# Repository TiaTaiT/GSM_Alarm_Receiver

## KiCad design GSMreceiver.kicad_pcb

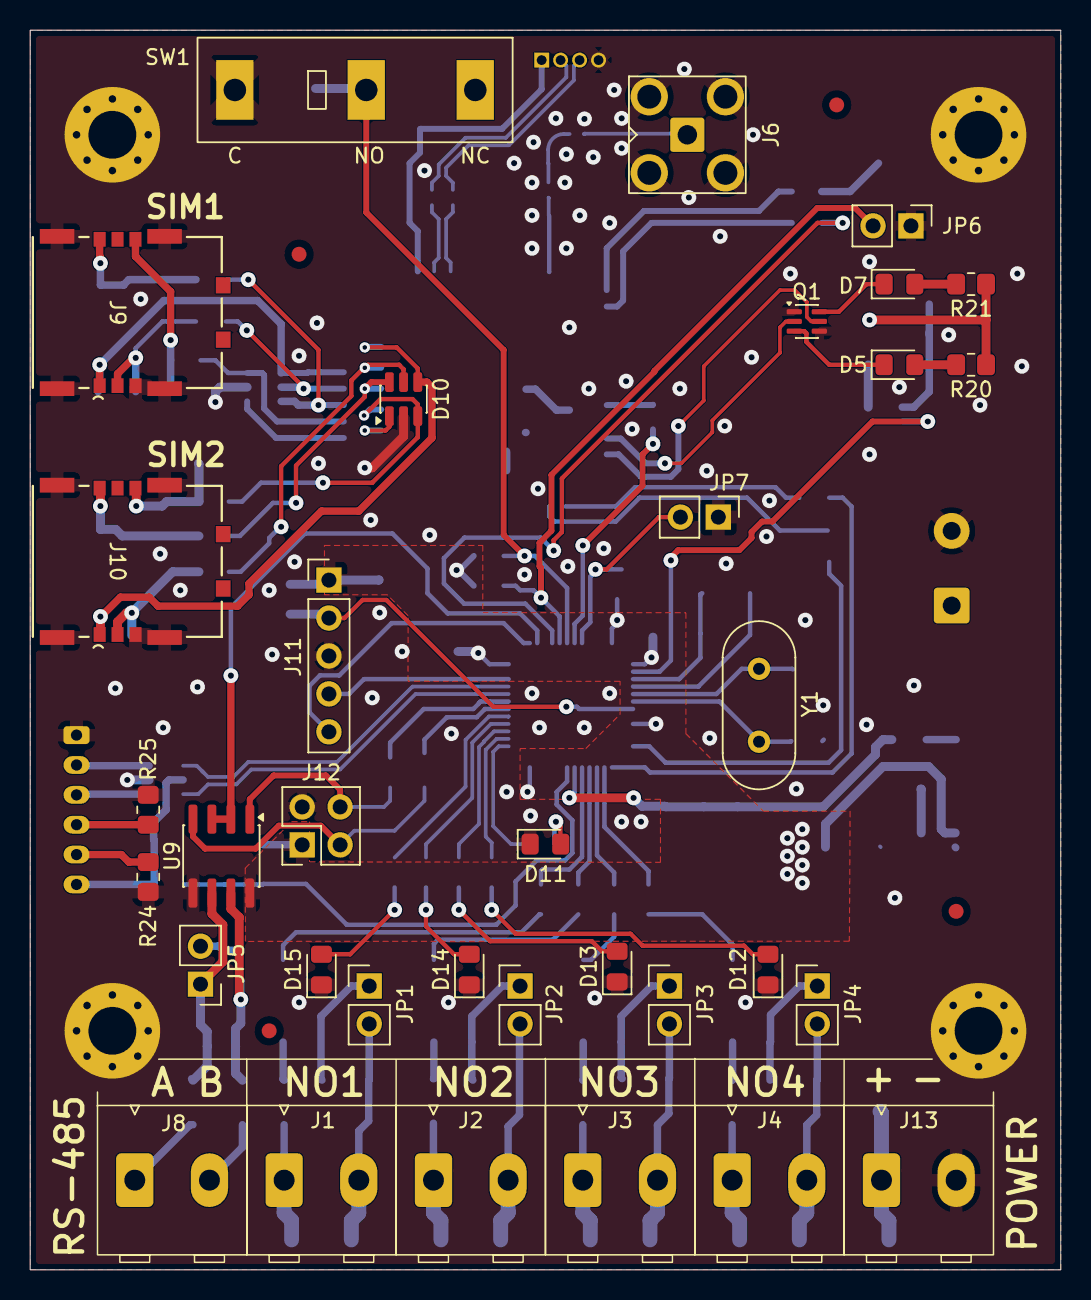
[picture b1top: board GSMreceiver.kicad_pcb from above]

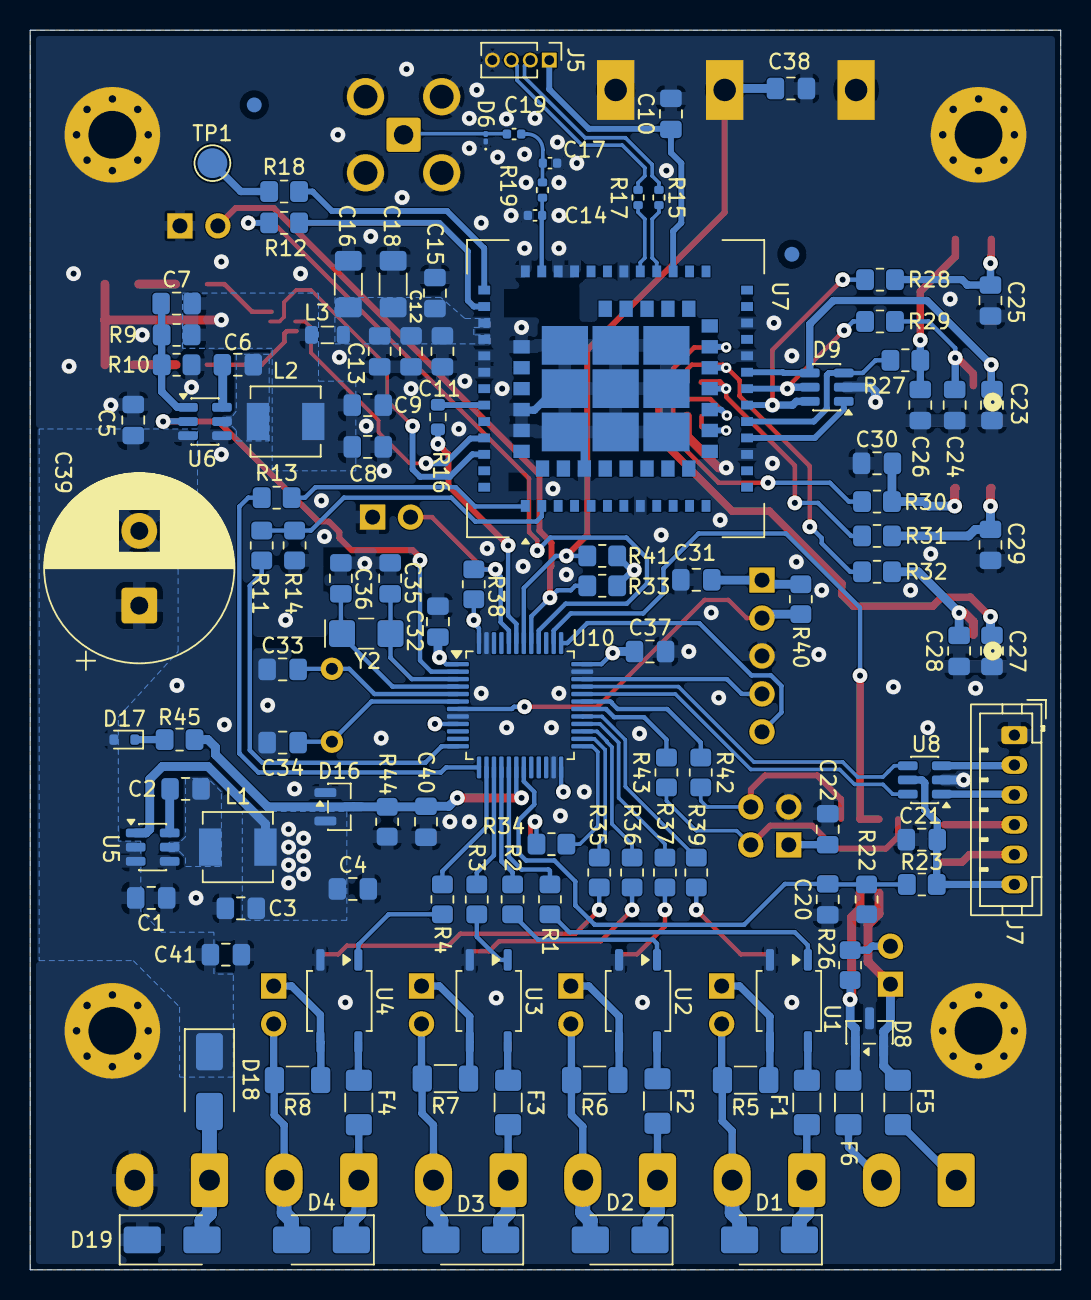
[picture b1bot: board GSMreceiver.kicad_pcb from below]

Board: 2 copper layers, 69.0 x 83.0 mm, 159 parts (117 on the bottom side), 116 nets.

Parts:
C1, C5: 10uF; C_0805_2012Metric_Pad1.18x1.45mm_HandSolder
C2, C6, C10, C13, C20, C21, C22, C23, C27, C31, C32, C37, C38, C40: 100nF; C_0805_2012Metric_Pad1.18x1.45mm_HandSolder
C3, C4, C8, C9: 22uF; C_0805_2012Metric_Pad1.18x1.45mm_HandSolder
C7: 100pF; C_0805_2012Metric_Pad1.18x1.45mm_HandSolder
C11: 10pF; C_0805_2012Metric_Pad1.18x1.45mm_HandSolder
C12: 33pF; C_0805_2012Metric_Pad1.18x1.45mm_HandSolder
C14, C17: 10pF; C_0402_1005Metric
C15: 1 uF; C_0805_2012Metric_Pad1.18x1.45mm_HandSolder
C16, C18: 100 uF; C_1206_3216Metric_Pad1.33x1.80mm_HandSolder
C19: 100pF; C_0402_1005Metric
C24, C25, C26, C28, C29, C30: 22pF; C_0805_2012Metric_Pad1.18x1.45mm_HandSolder
C33, C34: 20pF; C_0805_2012Metric_Pad1.18x1.45mm_HandSolder
C35, C36: 12.5pF; C_0805_2012Metric_Pad1.18x1.45mm_HandSolder
C39: 1000uFx35V; CP_Radial_D12.5mm_P5.00mm
C41: 470nFx50V; C_0805_2012Metric_Pad1.18x1.45mm_HandSolder
D1, D2, D3, D4, D19: SMAJ30CA; D_SMA
D5: STATUS; LED_0805_2012Metric_Pad1.15x1.40mm_HandSolder
D6: LXES1UTAA1-157; D_01005_0402Metric
D7: NETLIGHT; LED_0805_2012Metric_Pad1.15x1.40mm_HandSolder
D8: SM712-02HTG; SOT-23
D9, D10: ESDA6V1-5SC6; SOT-23-6
D11, D12, D13, D14: FYLS-0805GC; LED_0805_2012Metric_Pad1.15x1.40mm_HandSolder
D15: FYLS-0805SRC; LED_0805_2012Metric_Pad1.15x1.40mm_HandSolder
D16: BAS40-04; SOT-23
D17: 1N4148WT; D_SOD-523
D18: SS26; D_SMA
F1, F2, F3, F4, F5, F6: 1206L005/60WR; Fuse_1206_3216Metric_Pad1.42x1.75mm_HandSolder
FID1, FID2, FID3, FID4, FID5, FID6: Fiducial; Fiducial_1mm_Mask2mm
H1, H2, H3, H4: MountingHole_Pad; MountingHole_3.2mm_M3_Pad_Via
J1: Relay_1; DEGSON_DG390-5.0-02P_1x02_P5.0mm_Vertical
J2: Relay_2; DEGSON_DG390-5.0-02P_1x02_P5.0mm_Vertical
J3: Relay_3; DEGSON_DG390-5.0-02P_1x02_P5.0mm_Vertical
J4: Relay_4; DEGSON_DG390-5.0-02P_1x02_P5.0mm_Vertical
J5: USB_RF; PinHeader_1x04_P1.27mm_Vertical
J6: RF Antenna; SMA_HJ-SMA405
J7: USB-C; JST_PH_B6B-PH-K_1x06_P2.00mm_Vertical
J8: RS485; DEGSON_DG390-5.0-02P_1x02_P5.0mm_Vertical
J9, J10: 1042240820; 1042240820_MOLEX
J11: SWD; PinHeader_1x05_P2.54mm_Vertical
J12: UART1; PinSocket_2x02_P2.54mm_Vertical
J13: DG390-5.0-02P; DEGSON_DG390-5.0-02P_1x02_P5.0mm_Vertical
JP1, JP2, JP3, JP4, JP5, JP6, JP7: Jumper_2_Open; PinHeader_1x02_P2.54mm_Vertical
L1: CSAB0420-3R3M; CSAB0420-4.4x4.4mm
L2: CSAB0420-100M; CSAB0420-4.4x4.4mm
L3: BLM21PG300SN1D; L_0805_2012Metric
Q1: MUN5233DW1; SOT-363_SC-70-6
R1, R2, R3, R4: 2.7k; R_0805_2012Metric_Pad1.20x1.40mm_HandSolder
R5, R6, R7, R8: 4.7k; R_1206_3216Metric_Pad1.30x1.75mm_HandSolder
R9: 205k; R_0805_2012Metric_Pad1.20x1.40mm_HandSolder
R10: 51k; R_0805_2012Metric_Pad1.20x1.40mm_HandSolder
R11, R12, R13, R18: 1k; R_0805_2012Metric_Pad1.20x1.40mm_HandSolder
R14: 5.6k; R_0805_2012Metric_Pad1.20x1.40mm_HandSolder
R15, R17, R19: 0; R_0402_1005Metric
R16: 1k; R_0603_1608Metric
R20, R21: 470; R_0805_2012Metric_Pad1.20x1.40mm_HandSolder
R22: 47k; R_0805_2012Metric_Pad1.20x1.40mm_HandSolder
R23, R33, R38, R40, R41, R44: 100k; R_0805_2012Metric_Pad1.20x1.40mm_HandSolder
R24, R25: 5.1k; R_0805_2012Metric_Pad1.20x1.40mm_HandSolder
R26: 120; R_0805_2012Metric_Pad1.20x1.40mm_HandSolder
R27, R28, R29, R30, R31, R32, R42, R43: 51; R_0805_2012Metric_Pad1.20x1.40mm_HandSolder
R34, R35, R36, R37: 330; R_0805_2012Metric_Pad1.20x1.40mm_HandSolder
R39: 510; R_0805_2012Metric_Pad1.20x1.40mm_HandSolder
R45: 1M; R_0805_2012Metric_Pad1.20x1.40mm_HandSolder
SW1: SM5-180UP-1; SW_XKB_SM5-180UP-1
TP1: USB_BOOT; TestPoint_Pad_D2.0mm
U1, U2, U3, U4: PRAB34S; SOP-4_3.8x4.1mm_P2.54mm
U5: AP63203WU; TSOT-23-6
U6: AP63200WU; TSOT-23-6
U7: A7682E; SIMCom_A7682E_LGA-85
U8: USBLC6-2SC6; SOT-23-6
U9: XR3072XIDTR-F; SOIC-8_3.9x4.9mm_P1.27mm
U10: STM32L072CBT6; LQFP-48_7x7mm_P0.5mm
Y1: 4 MHz; Crystal_HC49-4H_Vertical
Y2: 32768 kHz; Crystal_SMD_EuroQuartz_EQ161-2Pin_3.2x1.5mm_HandSoldering

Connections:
+3V3: C3.2, C4.2, C22.2, C31.2, C32.2, C37.1, D16.2, J11.1, J12.1, L1.2, R33.1, R38.1, R40.1, R41.1, U5.1 (FB), U9.8 (VCC), U10.1 (VDD), U10.9 (VDDA), U10.24 (VDD), U10.36 (VDD_USB), U10.48 (VDD)
+4V: C7.2, C8.2, C9.2, L2.2, L3.2, R9.2, R20.1, R21.1
/4V_ENABLE: U6.2 (EN), U10.2 (PC13)
/BATTERY_LEVEL: C40.2, D16.3, R44.1, R45.1, U10.18 (PB0)
/DOUT1: R1.1, U10.17 (PA7)
/DOUT2: R2.1, U10.16 (PA6)
/DOUT3: R3.1, U10.15 (PA5)
/DOUT4: R4.1, U10.14 (PA4)
/IN_OUT/RELAY1A: D1.2 (A2), J1.2, JP1.2 (B), R5.2
/IN_OUT/RELAY1B: D1.1 (A1), F1.2, J1.1
/IN_OUT/RELAY2A: D2.2 (A2), J2.2, JP2.2 (B), R6.2
/IN_OUT/RELAY2B: D2.1 (A1), F2.2, J2.1
/IN_OUT/RELAY3A: D3.2 (A2), J3.2, JP3.2 (B), R7.2
/IN_OUT/RELAY3B: D3.1 (A1), F3.2, J3.1
/IN_OUT/RELAY4A: D4.2 (A2), J4.2, JP4.2 (B), R8.2
/IN_OUT/RELAY4B: D4.1 (A1), F4.2, J4.1
/MCU/BOOT0: JP7.2 (B), R38.2, U10.44 (BOOT0)
/MCU/LED1: R34.1, U10.25 (PB12)
/MCU/LED2: R35.1, U10.26 (PB13)
/MCU/LED3: R36.1, U10.27 (PB14)
/MCU/LED4: R37.1, U10.28 (PB15)
/MCU/LED5: R39.1, U10.29 (PA8)
/MCU/NRST: J11.2, R40.2, U10.7 (NRST)
/MCU/SWCLK: J11.5, U10.37 (PA14)
/MCU/SWDIO: J11.4, U10.34 (PA13)
/MCU/TAMPER: C38.2, R41.2, SW1.2 (B), U10.42 (PB6)
/MCU/VBUS_SENSING: C20.2, R22.1, R23.1, U10.19 (PB1)
/Power_3.3V (page 3)/3V3-BST: C2.1, U5.6 (BST)
/Power_3.3V (page 3)/3V3-SW: C2.2, L1.1, U5.5 (SW)
/Power_3.3V (page 3)/VBAT_IN: C1.2, C5.2, C39.1, C41.1, D17.2 (A), D18.1 (K), U5.2 (EN), U5.3 (IN), U6.3 (IN)
/Power_4V/4V-FB: C7.1, R9.1, R10.2, U6.1 (FB)
/Power_4V/4V-SW: C6.2, L2.1, U6.5 (SW)
/Power_input/Vsupply: D18.2 (A), D19.2 (A2), J13.1
/RF_ENABLE: R16.1, U10.43 (PB7)
/RF_RESET: R12.1, U10.40 (PB4)
/RFmodule/BOOT: R18.1, TP1.1 (1_1)
/RFmodule/NETLIGHT: Q1.2 (B), U7.41 (NETLIGHT)
/RFmodule/RF_USB_N: J5.2, R15.1
/RFmodule/RF_USB_P: J5.3, R17.1
/RFmodule/SIM1_CLK: D9.6 (IO5), R28.1, U7.16 (SIM1_CLK)
/RFmodule/SIM1_DATA: D9.3 (IO2), R27.1, U7.15 (SIM1_DATA)
/RFmodule/SIM1_DET: D9.1 (IO1), U7.14 (SIM1_DET)
/RFmodule/SIM1_RST: D9.5 (IO4), R29.1, U7.17 (SIM1_RST)
/RFmodule/SIM1_VDD: C23.2, D9.4 (IO3), J9.S1 (VCC), U7.18 (SIM1_VDD)
/RFmodule/SIM2_CLK: D10.6 (IO5), R31.1, U7.54 (SIM2_CLK)
/RFmodule/SIM2_DATA: D10.3 (IO2), R30.1, U7.53 (SIM2_DATA)
/RFmodule/SIM2_DET: D10.1 (IO1), U7.52 (SIM2_DET)
/RFmodule/SIM2_RST: D10.5 (IO4), R32.1, U7.55 (SIM2_RST)
/RFmodule/SIM2_VDD: C27.2, D10.4 (IO3), J10.S1 (VCC), U7.56 (SIM2_VDD)
/RFmodule/SIM_USB_N: R15.2, U7.25 (USB_DP)
/RFmodule/SIM_USB_P: R17.2, U7.26 (USB_DM)
/RFmodule/STATUS: Q1.5 (B), U7.42 (STATUS)
/RFmodule/USB_VBUS: C10.1, J5.1, U7.24 (USB_VBUS)
/RFmodule/VBAT: C11.2, C12.2, C13.2, C15.2, C16.2, C18.2, L3.1, U7.34 (VBAT), U7.35 (VBAT)
/RS485/RS485+: F5.2, J8.1
/RS485/RS485-: F6.2, J8.2
/RS485/RS485_N: D8.1 (A1), F6.1, R26.1, U9.7 (B)
/RS485/RS485_P: D8.2 (A2), F5.1, JP5.1 (A), U9.6 (A)
/RS485_EN: U9.2 (~RE), U9.3 (DE), U10.38 (PA15)
/SIMcard1/CARD_CLK: C25.2, J9.S3 (CLK), R28.2
/SIMcard1/CARD_DATA: C26.2, J9.S6 (I/O), R27.2
/SIMcard1/CARD_RST: C24.2, J9.S2 (RST), R29.2
/SIMcard2/CARD_CLK: C29.2, J10.S3 (CLK), R31.2
/SIMcard2/CARD_DATA: C30.2, J10.S6 (I/O), R30.2
/SIMcard2/CARD_RST: C28.2, J10.S2 (RST), R32.2
/UART1_RX: J12.4, R42.2, U9.1 (RO)
/UART1_TX: J12.2, R43.2, U9.4 (DI)
/UART2_RX: R13.1, U10.13 (PA3)
/UART2_TX: R11.1, U10.12 (PA2)
/USB/USB_CC1: J7.5, R24.1
/USB/USB_CC2: J7.4, R25.1
/USB/USB_N: J7.3, U8.1 (I/O1)
/USB/USB_P: J7.2, U8.3 (I/O2)
/USB/USB_VBUS: C21.2, J7.6, R23.2, U8.5 (VBUS)
/USB_D+: U8.4 (I/O2), U10.33 (PA12)
/USB_D-: U8.6 (I/O1), U10.32 (PA11)
GNDD: C1.1, C3.1, C4.1, C5.1, C8.1, C9.1, C10.2, C11.1, C12.1, C13.1, C14.1, C15.1, C16.1, C17.1, C18.1, C20.1, C21.1, C22.1, C23.1, C24.1, C25.1, C26.1, C27.1, C28.1, C29.1, C30.1, C31.1, C32.1, C33.1, C34.1, C35.1, C36.1, C37.2, C38.1, C39.2, C40.1, C41.2, D6.1 (A1), D8.3 (common), D9.2 (GND), D10.2 (GND), D11.1 (K), D12.1 (K), D13.1 (K), D14.1 (K), D15.1 (K), D16.1, D19.1 (A1), H1.1 (1_1), H2.1 (1_1), H3.1 (1_1), H4.1 (1_1), J5.4, J6.2 (Ext), J7.1, J9.G (SH), J9.S4 (GND), J10.G (SH), J10.S4 (GND), J11.3, J12.3, J13.2, JP6.1 (A), JP7.1 (A), Q1.1 (E), Q1.4 (E), R10.1, R14.1, R22.2, R24.2, R25.2, R44.2, SW1.1 (A), U1.2 (C), U2.2 (C), U3.2 (C), U4.2 (C), U5.4 (GND), U6.4 (GND), U7.8 (GND), U7.13 (GND), U7.19 (GND), U7.21 (GND), U7.27 (GND), U7.30 (GND), U7.31 (GND), U7.33 (GND), U7.36 (GND), U7.37 (GND), U7.45 (GND), U7.63 (GND), U7.66 (GND), U7.67 (GND), U7.69 (GND), U7.70 (GND), U7.71 (GND), U7.72 (GND), U7.73 (GND), U7.74 (GND), U7.75 (GND), U7.76 (GND), U7.77 (GND), U8.2 (GND), U9.5 (GND), U10.8 (VSSA), U10.23 (VSS), U10.35 (VSS), U10.47 (VSS)
unnamed: C17.2, C19.2, R19.2
unnamed: D5.2 (A), R20.2
unnamed: D5.1 (K), Q1.3 (C)
unnamed: C19.1, D6.2 (A2), J6.1 (In)
unnamed: D7.2 (A), R21.2
unnamed: D7.1 (K), Q1.6 (C)
unnamed: D11.2 (A), R34.2
unnamed: D12.2 (A), R35.2
unnamed: D13.2 (A), R36.2
unnamed: D14.2 (A), R37.2
unnamed: D15.2 (A), R39.2
unnamed: D17.1 (K), R45.2
unnamed: JP1.1 (A), R5.1, U1.3 (VCC)
unnamed: JP2.1 (A), R6.1, U2.3 (VCC)
unnamed: JP3.1 (A), R7.1, U3.3 (VCC)
unnamed: JP4.1 (A), R8.1, U4.3 (VCC)
unnamed: JP5.2 (B), R26.2
unnamed: JP6.2 (B), R33.2, U10.41 (PB5)
unnamed: R1.2, U1.1 (A)
unnamed: F1.1, U1.4 (VEE)
unnamed: R2.2, U2.1 (A)
unnamed: F2.1, U2.4 (VEE)
unnamed: R3.2, U3.1 (A)
unnamed: F3.1, U3.4 (VEE)
unnamed: R4.2, U4.1 (A)
unnamed: F4.1, U4.4 (VEE)
unnamed: C6.1, U6.6 (BST)
unnamed: R18.2, U7.82 (BOOT_CFG)
unnamed: C14.2, R19.1, U7.32 (RF_ANT)
unnamed: R11.2, R14.2, U7.2 (UART1_RXD)
unnamed: R13.2, U7.1 (UART1_TXD)
unnamed: R16.2, U7.39 (~PWRKEY)
unnamed: R12.2, U7.83 (~RESET)
unnamed: R43.1, U10.30 (PA9)
unnamed: R42.1, U10.31 (PA10)
unnamed: C35.2, U10.3 (PC14), Y2.2
unnamed: C36.2, U10.4 (PC15), Y2.1
unnamed: C33.2, U10.5 (PH0), Y1.2
unnamed: C34.2, U10.6 (PH1), Y1.1

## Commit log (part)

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2025-04-16 USB pinout fixed
2025-07-28 Minor changes in PCB for manufacturing
2025-11-07 DEGSON f.mask pad fixed
2026-03-19 Move to SIM800C-DS and two SIM
2026-03-21 Kicad 10 update
2026-03-21 Fiducial position move to the observable area
2026-03-24 Release candidate
2026-04-10 Proproduction version
